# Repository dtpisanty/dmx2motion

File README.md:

# dmx2motion
An ESP32 based open-hardware project to control varing frequency AC motror drivers through DMX, ArtNet, OSC and MQTT

## Circuit board files
Schematics and PCB files were created using DIP Trace

## Library dependencies
This project uses Lukas Salomons ESP32-DMX Library https://github.com/luksal/ESP32-DMX and ThingPulse's ssd1306 OLED driver https://github.com/ThingPulse/esp8266-oled-ssd1306

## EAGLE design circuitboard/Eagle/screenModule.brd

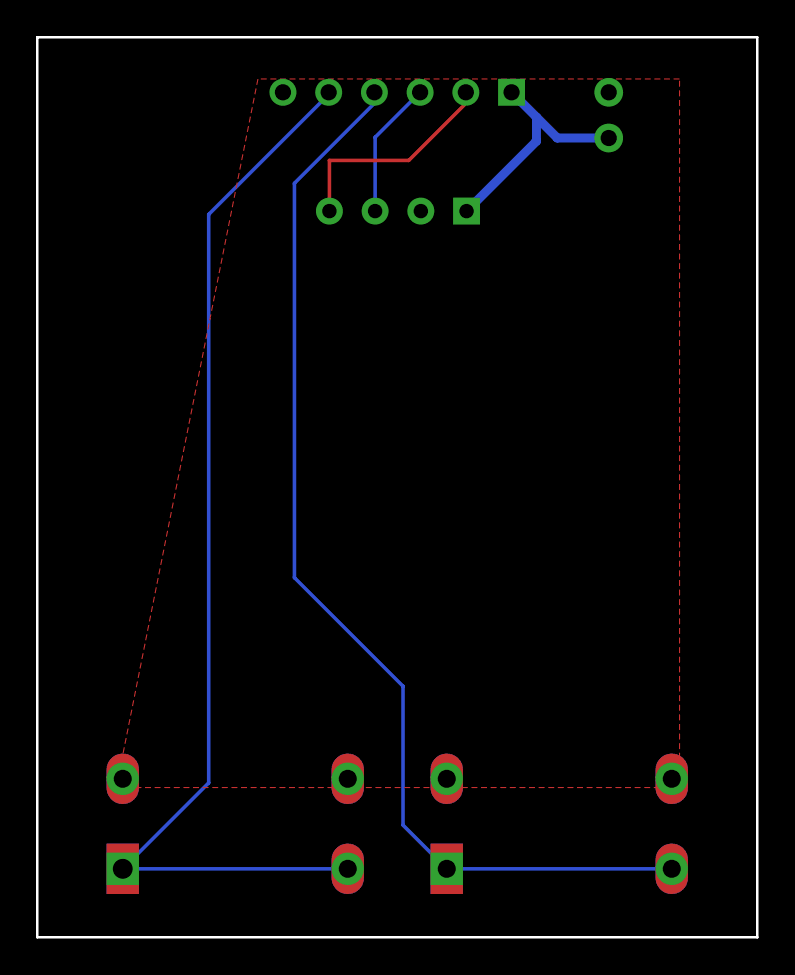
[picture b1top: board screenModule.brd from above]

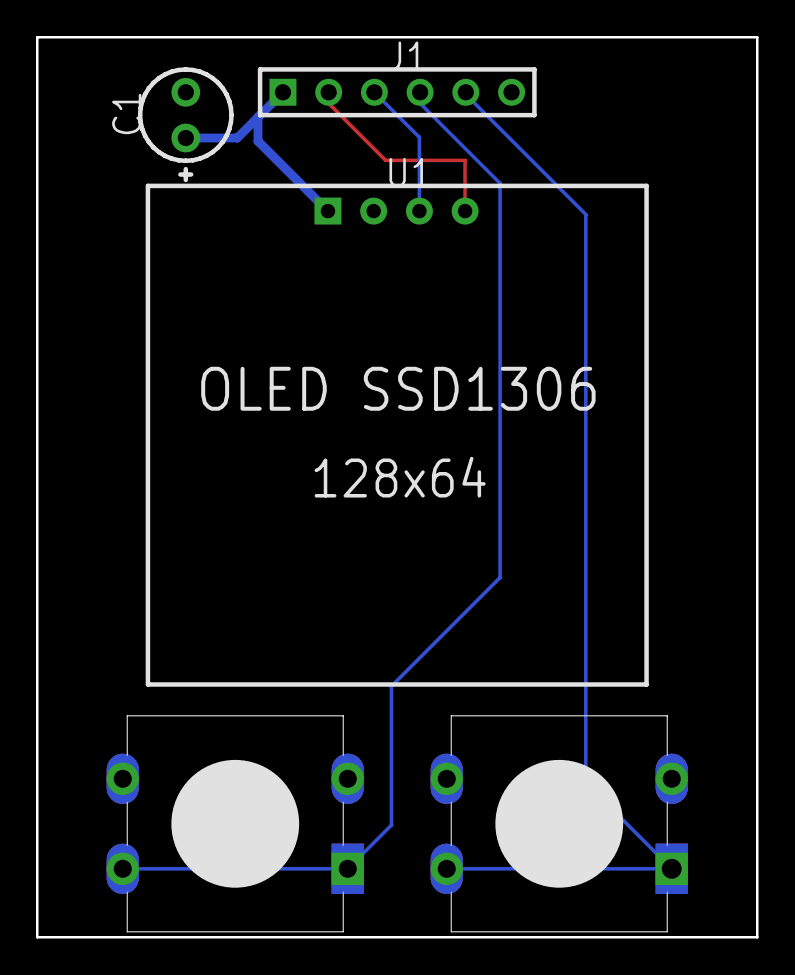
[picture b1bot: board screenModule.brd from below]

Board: 2 copper layers, 40.0 x 50.0 mm, 11 parts (11 on the bottom side), 6 nets.

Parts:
C1: 4.7uF; CAPPR-2.54/5.08
J1: HDR-1X6; HDR-1x6
PAD1: PAD; PAD_PAD1
PAD2, PAD3, PAD4, PAD6, PAD7, PAD8: PAD; PAD_PAD2
PAD5: PAD
U1: OLED SSD1306 128X64; OLED_SSD1306

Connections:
Net_0: C1.2, J1.6, PAD3.3, PAD4.4, PAD7.3, PAD8.4, U1.2
Net_1: C1.1, J1.1, U1.1
Net_2: J1.2, U1.4
Net_3: J1.3, U1.3
Net_5: J1.5, PAD1.1, PAD2.2
Net_6: J1.4, PAD5.1, PAD6.2

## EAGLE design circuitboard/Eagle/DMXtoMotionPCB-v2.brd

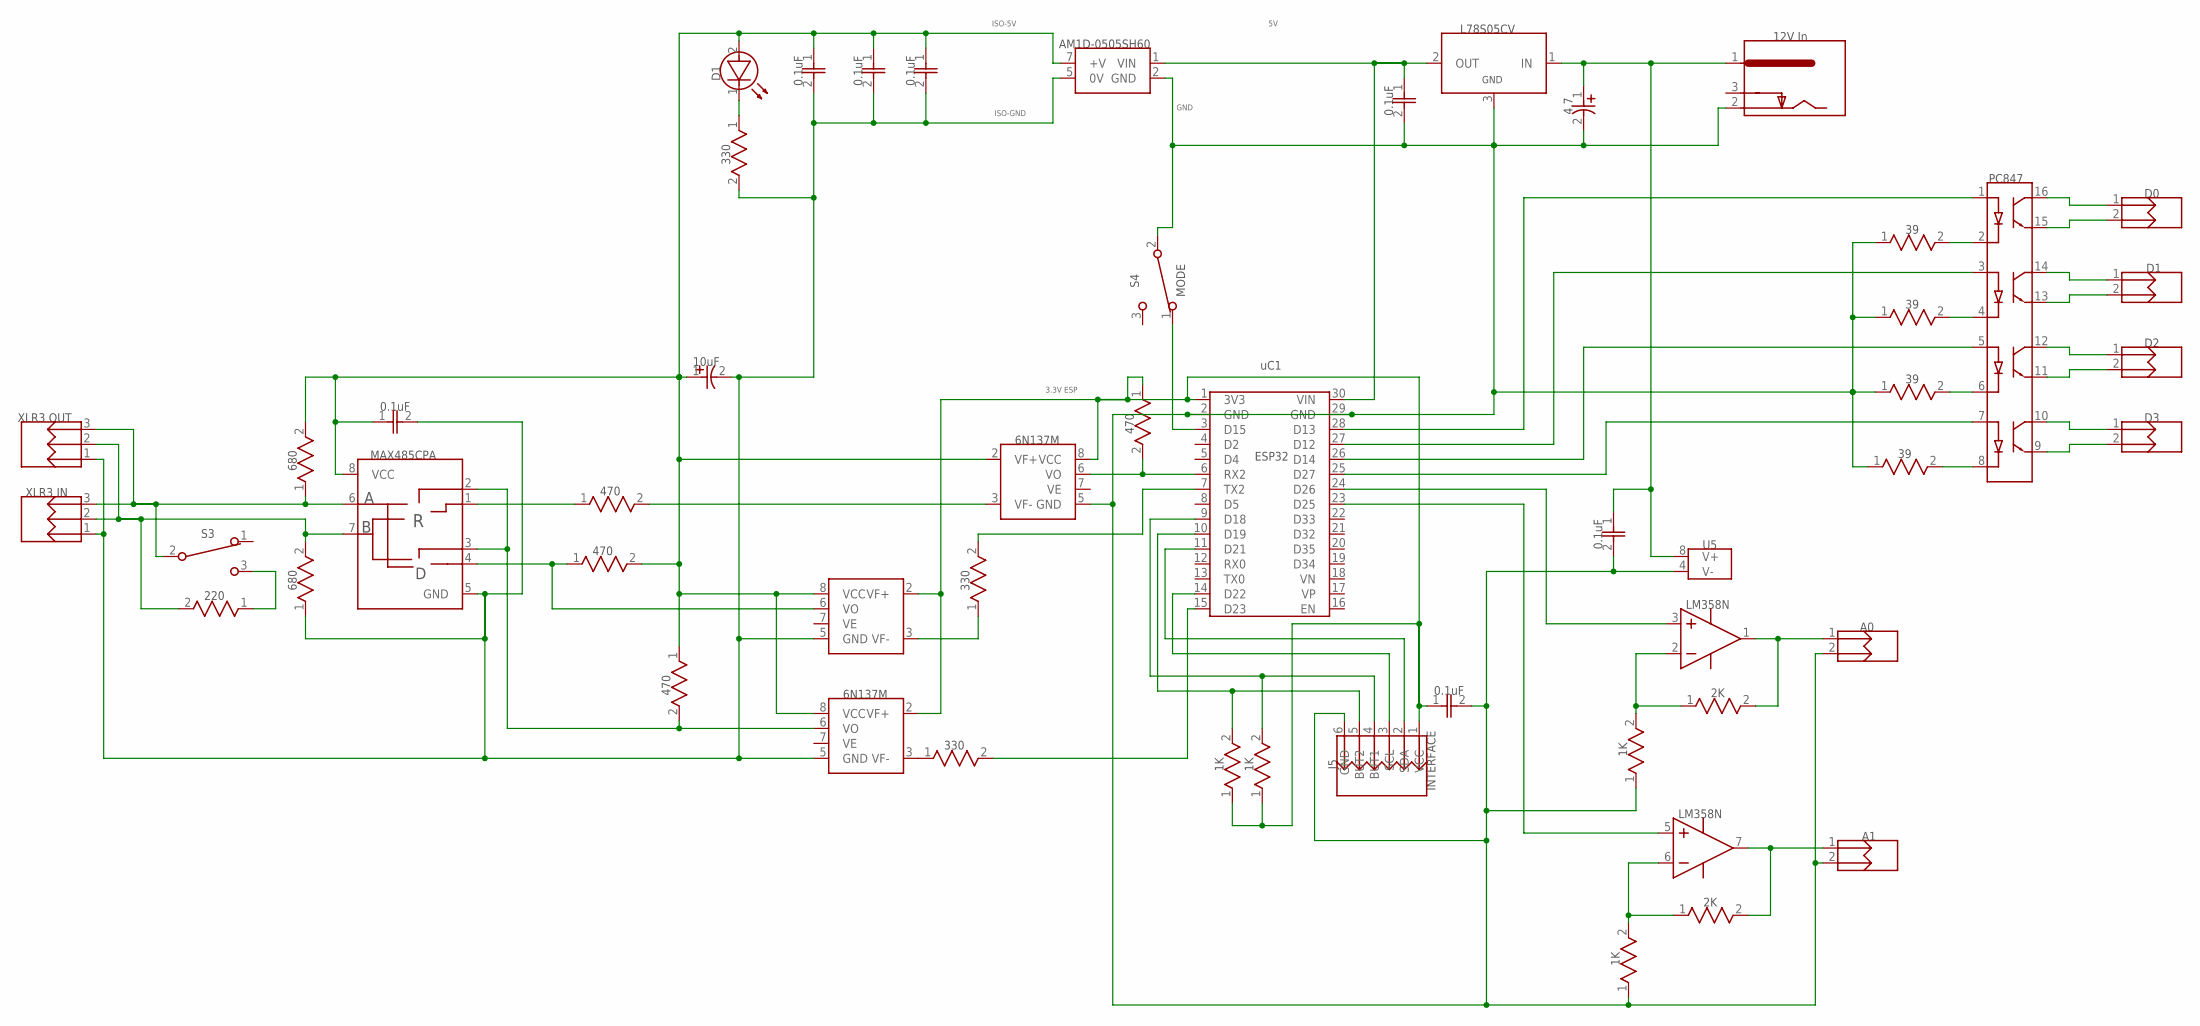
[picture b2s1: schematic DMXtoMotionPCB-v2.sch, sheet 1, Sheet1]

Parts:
C1, C2, C3, C6, C7, C8, C9: 0.1uF; CAP-5.08/9.15X3
C4: 4.7; CAPPR-2.54/5.08
C5: 10uF; CAPPR-2.54/5.08
D1: LED; LED100
J1: 12V In; 4840-2211
J2: XLR3 IN; HDR-1X3
J3: XLR3 OUT; HDR-1X3
J4: D1; HDR-1X2
J5: INTERFACE; HDR-1X6
J6: A0; HDR-1X2
J7: A1; HDR-1X2
J8: D0; HDR-1X2
J9: D3; HDR-1X2
J10: D2; HDR-1X2
R1, R2, R3: 330; RES-12.7/7.6X2.5
R4, R5, R6, R13: 470; RES-12.7/7.6X2.5
R7, R8: 680; RES-12.7/7.6X2.5
R9, R10, R18, R20: 1K; RES-12.7/7.6X2.5
R12: 220; RES-12.7/7.6X2.5
R14, R15, R16, R17: 39; RES-12.7/7.6X2.5
R19, R21: 2K; RES-12.7/7.6X2.5
S3: SWITCH_SPDT; HDRF-1X3T/2.54/8X3
S4: MODE; HDRF-1X3T/2.54/8X3
U1: AM1D-0505SH60; SIP-4(7)/19.5X6X2.54
U2: MAX485CPA; DIP-8
U4: L78S05CV; TO-220V
U5: LM358N; DIP-8
VO1: 6N137M; DIP-8
VO2, VO3: 6N137M_10; DIP-8
VO4: PC847; DIP-16
uC1: ESP32-WROOM-DEVKITV1; ESP32-DEVKITV1

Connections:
3.3V_ESP: C7.1, J5.1 (VCC), R9.1 (A), R10.1 (A), R13.1 (A), VO1.8 (VCC), VO2.2 (VF+), VO3.2 (VF+), uC1.1 (3V3)
5V: C9.1, U1.1 (VIN), U4.2 (OUT), uC1.30 (VIN)
12V: C4.1 (PLUS), C6.1, J1.1, U4.1 (IN), U5.8 (V+)
But1: J5.4 (BUT1), R10.2 (B), uC1.9 (D18)
But2: J5.5 (BUT2), R9.2 (B), uC1.10 (D19)
GND: C4.2 (MINUS), C6.2, C7.2, C9.2, J1.2, J5.6 (GND), J6.2, J7.2, R14.1 (A), R15.1 (A), R16.1 (A), R17.1 (A), R18.1 (A), R20.1 (A), S4.2 (C1), U1.2 (GND), U4.3 (GND), U5.4 (V-), VO1.5 (GND), uC1.2 (GND), uC1.29 (GND)
ISO-5V: C1.1, C2.1, C3.1, C5.1 (PLUS), C8.1, D1.2 (A), R5.2 (B), R6.1 (A), R7.2 (B), U1.7 (+V), U2.8 (VCC), VO1.2 (VF+), VO2.8 (VCC), VO3.8 (VCC)
ISO-GND: C1.2, C2.2, C3.2, C5.2 (MINUS), C8.2, J2.1, J3.1, R1.2 (B), R8.1 (A), U1.5 (0V), U2.5 (GND), VO2.5 (GND), VO3.5 (GND)
Net_0: R17.2 (B), VO4.2 (Cathode)
Net_1: VO4.5 (Anode), uC1.26 (D14)
Net_2: VO4.7 (Anode), uC1.25 (D27)
Net_4: D1.1 (K), R1.1 (A)
Net_6: VO4.1 (Anode), uC1.28 (D13)
Net_7: VO4.3 (Anode), uC1.27 (D12)
Net_8: U5.5 (IN+), uC1.23 (D25)
Net_9: R2.1 (A), VO2.3 (VF-)
Net_10: R3.2 (B), uC1.15 (D23)
Net_11: R3.1 (A), VO3.3 (VF-)
Net_12: R4.2 (B), VO1.3 (VF-)
Net_13: R4.1 (A), U2.1 (RO)
Net_14: R6.2 (B), U2.2 (!RE), U2.3 (DE), VO3.6 (VO)
Net_15: R5.1 (A), U2.4 (DI), VO2.6 (VO)
Net_16: J2.2, J3.2, R8.2 (B), R12.2 (B), U2.7 (B)
Net_17: J2.3, J3.3, R7.1 (A), S3.2 (C1), U2.6 (A)
Net_18: J7.1, R19.2 (B), U5.7 (OUT)
Net_21: R18.2 (B), R19.1 (A), U5.6 (IN-)
Net_22: S4.1 (C2), uC1.3 (D15)
Net_24: U5.3 (IN+), uC1.24 (D26)
Net_32: J5.2 (SDA), uC1.11 (D21)
Net_33: J5.3 (SCL), uC1.14 (D22)
Net_34: R12.1 (A), S3.3 (C3)
Net_35: R14.2 (B), VO4.4 (Cathode)
Net_36: R15.2 (B), VO4.6 (Cathode)
Net_37: R16.2 (B), VO4.8 (Cathode)
Net_38: J8.2, VO4.15 (Emitter)
Net_39: J8.1, VO4.16 (Collector)
Net_40: J4.1, VO4.14 (Collector)
Net_41: J4.2, VO4.13 (Emitter)
Net_42: J10.1, VO4.12 (Collector)
Net_43: J10.2, VO4.11 (Emitter)
Net_44: J9.1, VO4.10 (Collector)
Net_45: J9.2, VO4.9 (Emitter)
Net_46: J6.1, R21.2 (B), U5.1 (OUT)
Net_47: R20.2 (B), R21.1 (A), U5.2 (IN-)
RX: R13.2 (B), VO1.6 (VO), uC1.6 (RX2)
TX: R2.2 (B), uC1.7 (TX2)

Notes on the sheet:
0.1uF
4.7
10uF
12V In
XLR3 IN
XLR3 OUT
INTERFACE
330
470
680
220
MODE
AM1D-0505SH60
MAX485CPA
GND
L78S05CV
LM358N
ESP32
uC1
6N137M
PC847
3.3V ESP
ISO-5V
ISO-GND

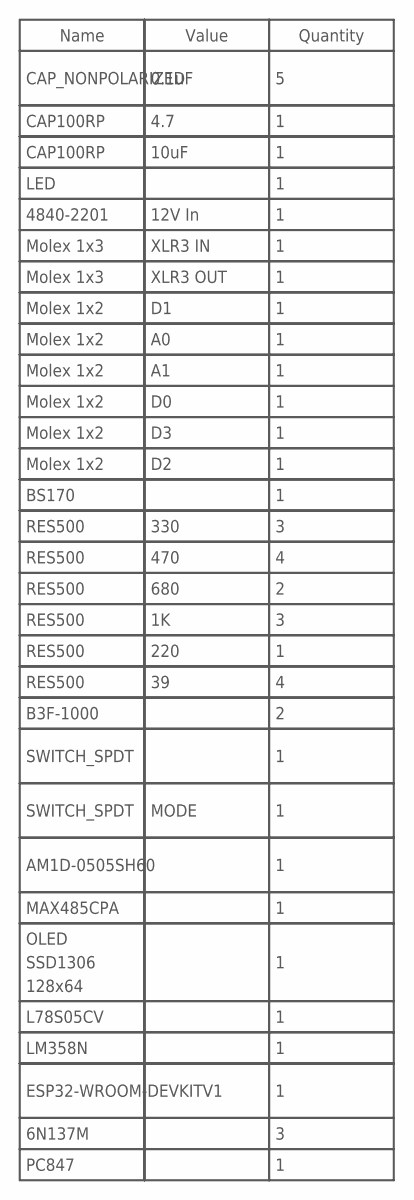
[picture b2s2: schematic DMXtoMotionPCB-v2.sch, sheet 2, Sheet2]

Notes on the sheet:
Name
CAP_NONPOLARIZED
CAP100RP
LED
4840-2201
Molex 1x3
Molex 1x2
BS170
RES500
B3F-1000
SWITCH_SPDT
AM1D-0505SH60
MAX485CPA
OLED SSD1306 128x64
L78S05CV
LM358N
ESP32-WROOM-DEVKITV1
6N137M
PC847
Value
0.1uF
4.7
10uF
12V In
XLR3 IN
XLR3 OUT
330
470
680
220
MODE
Quantity

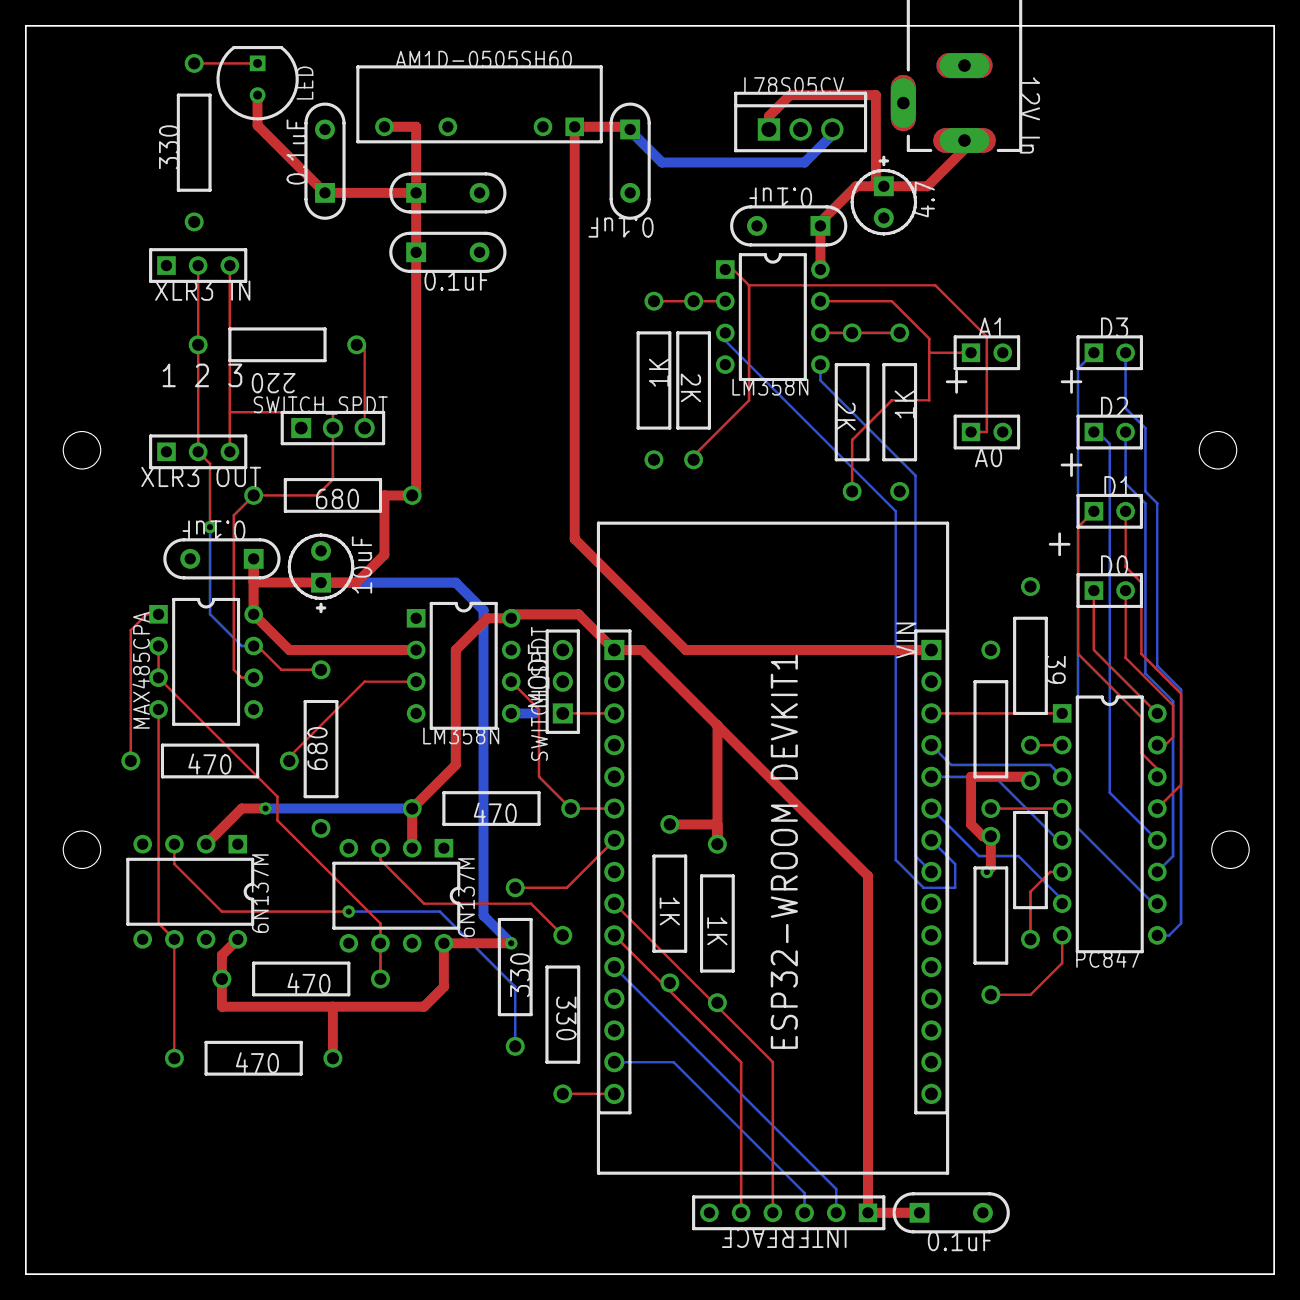
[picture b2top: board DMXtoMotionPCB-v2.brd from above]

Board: 2 copper layers, 100.0 x 100.0 mm, 51 parts (0 on the bottom side), 46 nets.

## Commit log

2021-11-04 Modified the schematic to include the following features: * Added 2 additional digital outputs * Replaced relay output with BPJ optocoupler * Replaced PWM output with 2 DAC outputs passing through an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
2022-04-01 Finished designing and routing version 2
2022-04-01 removed useless files
2022-04-01 updated gerber files
2025-01-31 update files to latest version. MAJOR CHANGES
2025-02-01 Added KiCAD and Eagle PCB files. Updated KiCAD main board to V3
2025-02-04 Slight modifications on KiCAD V3 files. Generated fabrication files
2025-02-05 Changes of through hole diameters in KiCAD V3 and BOM
2025-02-05 KiCAD files
2025-02-05 lista de materiales semiactualizada
2025-02-05 double checked through holes and part names. Completed BOM
2025-02-05 trace adjustments
2025-02-06 Actualización de componentes obsoletos
2025-02-06 Actualización de lista de componentes
